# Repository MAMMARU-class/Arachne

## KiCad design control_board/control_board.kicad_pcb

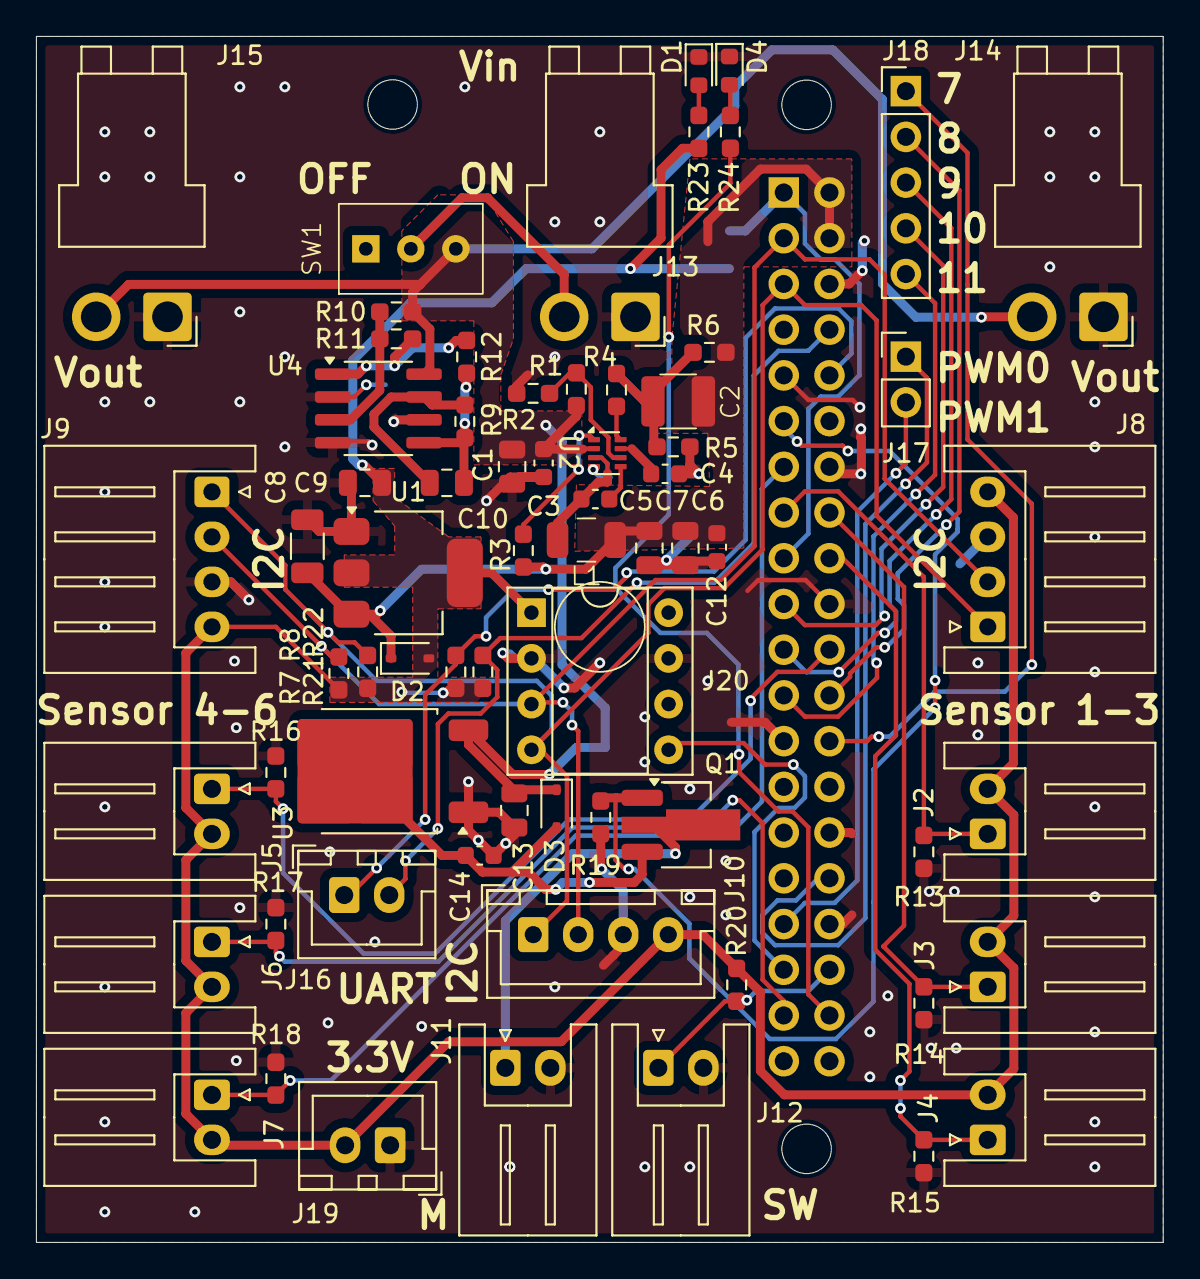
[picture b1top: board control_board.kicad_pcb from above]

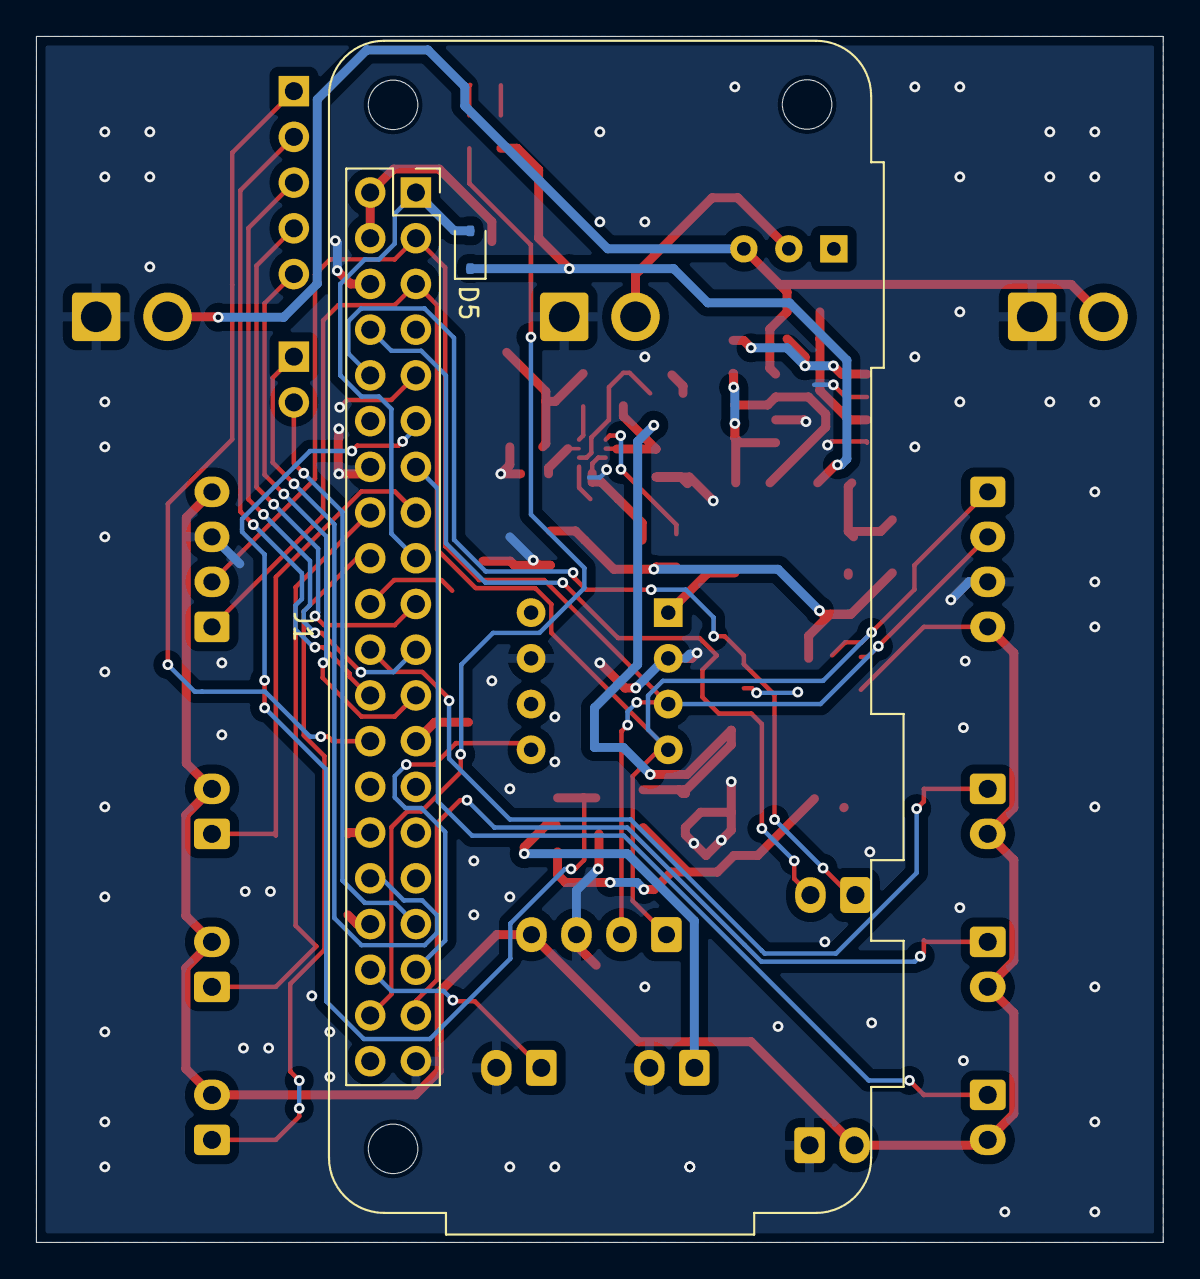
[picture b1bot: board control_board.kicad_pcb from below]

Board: 2 copper layers, 62.6 x 67.0 mm, 69 parts (2 on the bottom side), 42 nets.

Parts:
C1, C6, C7, C9: 22u/25V/2012; C_0805_2012Metric
C2: 300p/200V/1111; Capacitor_SMD_2.7x2.7
C3, C5, C12, C14: 0.1u/25V/1608; C_0603_1608Metric
C4: 22n/50V/1608; C_0603_1608Metric
C8: 10u/50V/3216; C_1206_3216Metric
C10, C13: 1u/50V/2012; C_0805_2012Metric
D1: GREEN; LED_0603_1608Metric
D2, D3, D5: CUHS20S60/2A/60V; D_SOD-323
D4: RED; LED_0603_1608Metric
J1: Raspberry_Pi_2_3; Raspberry_Pi_Zero_Socketed_THT_FaceDown_MountingHoles_with_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
J2, J3, J4, J5, J6, J7: pressur_sensor; JST_XH_S2B-XH-A_1x02_P2.50mm_Horizontal
J8: I2C_signal_wire; JST_XH_S4B-XH-A_1x04_P2.50mm_Horizontal
J9: I2C signal wire; JST_XH_S4B-XH-A_1x04_P2.50mm_Horizontal
J10: I2C signal wire; JST_XH_B4B-XH-A_1x04_P2.50mm_Vertical
J11: motor_control; JST_XH_S2B-XH-A_1x02_P2.50mm_Horizontal
J12: limit_switch; JST_XH_S2B-XH-A_1x02_P2.50mm_Horizontal
J13: Vin; JST_VH_B2PS-VH_1x02_P3.96mm_Horizontal
J14, J15: Vout; JST_VH_B2PS-VH_1x02_P3.96mm_Horizontal
J16: UART; JST_XH_B2B-XH-A_1x02_P2.50mm_Vertical
J17: PWM; PinHeader_1x02_P2.54mm_Vertical
J18: GPIO(7~11); PinHeader_1x05_P2.54mm_Vertical
J19: +3.3Vout; JST_XH_B2B-XH-A_1x02_P2.50mm_Vertical
J20: AE_BNO055_BO; DIP-8_W7.62mm_Socket
L1: 6.8u; L_NLV32-PF_SMD_3.2x2.5_handsolder
Q1: 2SC4703; SOT-89-3_Handsoldering
R1: 191k; R_0603_1608Metric_Pad0.98x0.95mm_HandSolder
R2: 49.9k; R_0603_1608Metric_Pad0.98x0.95mm_HandSolder
R3, R4, R5, R7, R8, R9, R10, R11, R13, R14, R15, R16, R17, R18, R19, R21, R22: 10k; R_0603_1608Metric_Pad0.98x0.95mm_HandSolder
R6: 90.9k; R_0603_1608Metric_Pad0.98x0.95mm_HandSolder
R12: 40k; R_0603_1608Metric_Pad0.98x0.95mm_HandSolder
R20: 5k; R_0603_1608Metric_Pad0.98x0.95mm_HandSolder
R23, R24: 510; R_0603_1608Metric_Pad0.98x0.95mm_HandSolder
SW1: power_switch; Toggle_Switch_2MS1-T1-B4-M2-Q-E
U1: AZ1117-3.3; SOT-223-3_TabPin2
U2: MP2338; SOT-583-8
U3: NJM78055DL1; TO-252-2
U4: LM2904GD; SOP-8_3.76x4.96mm_P1.27mm

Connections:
+3.3V: C9.1, D2.2 (A), D5.1 (K), J2.2, J3.2, J4.2, J5.2, J6.2, J7.2, J8.4, J9.4, J10.4, J19.2, J20.1 (VIN), R7.1, R8.1, R20.2, R21.1, R22.1, R23.1, U1.2 (VO)
+5V: C2.2, C6.1, C7.1, C8.1, C12.1, D2.1 (K), J1.2 (5V), J1.4 (5V), L1.2, R3.1, R6.2, U1.3 (VI)
/7: J1.26 (~CE1/GPIO7), J18.1
/8: J1.24 (~CE0/GPIO8), J18.2
/9: J1.21 (MISO0/GPIO9), J18.3
/10: J1.19 (MOSI0/GPIO10), J18.4
/11: J1.23 (SCLK0/GPIO11), J18.5
/12: J1.32 (PWM0/GPIO12), J17.1
/13: J1.33 (PWM1/GPIO13), J17.2
/BNO055_reset: J1.35 (GPIO19/MISO1), J20.5 (RESET)
/Press1: J1.15 (GPIO22), J2.1, R13.2
/Press2: J1.16 (GPIO23), J3.1, R14.2
/Press3: J1.18 (GPIO24), J4.1, R15.2
/Press4: J1.22 (GPIO25), J5.1, R16.2
/Press5: J1.37 (GPIO26), J6.1, R17.2
/Press6: J1.13 (GPIO27), J7.1, R18.2
/RX: J1.10 (GPIO15/RXD), J16.1, R21.2
/SCL: J1.5 (SCL/GPIO3), J8.1, J9.1, J10.1, J20.4 (SCL/R), R7.2
/SDA: J1.3 (SDA/GPIO2), J8.2, J9.2, J10.2, J20.3 (SDA/T), R8.2
/TX: J1.8 (GPIO14/TXD), J16.2, R22.2
/limit_switch: J1.36 (GPIO16), J12.1, R20.1
/motor_control: J1.11 (GPIO17), Q1.1 (B), R19.1
/supply detection: C10.1, R9.1, U4.7
GND: C1.2, C3.2, C4.2, C6.2, C7.2, C8.2, C9.2, C12.2, C13.2, C14.2, D1.1 (K), D4.1 (K), J1.6 (GND), J1.9 (GND), J1.14 (GND), J1.20 (GND), J1.25 (GND), J1.30 (GND), J1.34 (GND), J1.39 (GND), J8.3, J9.3, J10.3, J11.2, J12.2, J13.1, J14.1, J15.1, J19.1, J20.2 (GND), J20.7 (GND), R2.2, R5.2, R13.1, R14.1, R15.1, R16.1, R17.1, R18.1, R19.2, U1.1 (GND), U2.4 (GND), U3.1 (GND), U4.2 (-), U4.4 (GND), U4.6 (-)
unnamed: C2.1, R4.2, R5.1, R6.1
unnamed: C10.2, R9.2, R12.2, U4.5 (+)
unnamed: D1.2 (A), R23.2
unnamed: C14.1, D3.2 (A), Q1.3 (C), U3.2 (VO)
unnamed: D4.2 (A), R24.2
unnamed: D5.2 (A), J1.1 (3V3), J1.17 (3V3)
unnamed: J1.38 (GPIO20/MOSI1), R24.1
unnamed: J11.1, Q1.2 (E)
unnamed: J13.2, SW1.2 (B)
unnamed: R10.1, R11.1, U4.3 (+)
unnamed: R11.2, R12.1, U4.1
unnamed: C5.2, U2.5 (BST)
unnamed: R1.2, R2.1, U2.6 (EN)
unnamed: R4.1, U2.8 (FB)
unnamed: R3.2, U2.1 (PG)
unnamed: C4.1, U2.7 (SS)
unnamed: C5.1, L1.1, U2.3 (SW)
VDD: C1.1, C3.1, C13.1, D3.1 (K), J14.2, J15.2, R1.1, R10.2, SW1.3 (C), U2.2 (VIN), U3.3 (VI), U4.8 (VCC)

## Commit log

2024-09-03 create control bo board
2025-04-25 first cmmit
